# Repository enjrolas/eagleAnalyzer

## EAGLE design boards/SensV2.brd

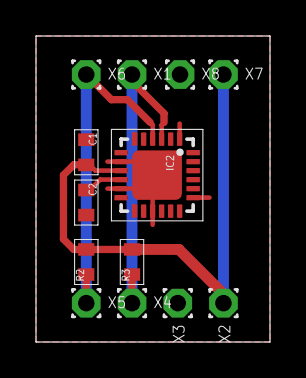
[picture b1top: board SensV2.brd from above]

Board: 2 copper layers, 13.0 x 17.0 mm, 13 parts (0 on the bottom side), 5 nets.

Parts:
C1: 100n; 0603
C2: 4u7; 0603
IC2: QFN24
R2, R3: 4k7; 0603
X1, X3, X4, X5, X6, X8: GND; T1.6/0.9
X2, X7: 3v3; T1.6/0.9

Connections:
+3V3: C1.2, IC2.9, R2.2, R3.2, X2.1, X7.1
GND: C1.1, C2.2, IC2.1, IC2.8, IC2.11, IC2.15, IC2.19, IC2.EXP, X3.1, X8.1
unnamed: C2.1, IC2.10
SCL: IC2.3, R3.1, X1.1, X4.1
SDA: IC2.4, R2.1, X5.1, X6.1

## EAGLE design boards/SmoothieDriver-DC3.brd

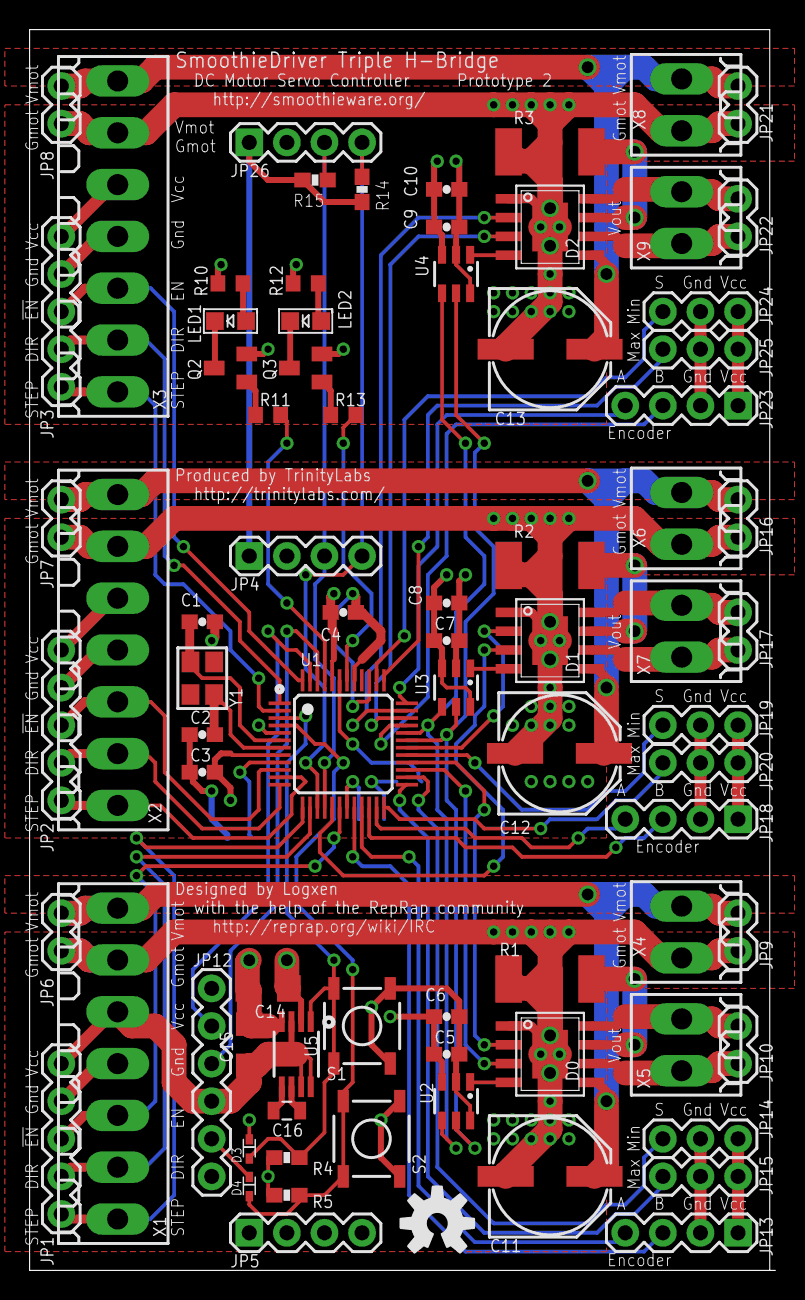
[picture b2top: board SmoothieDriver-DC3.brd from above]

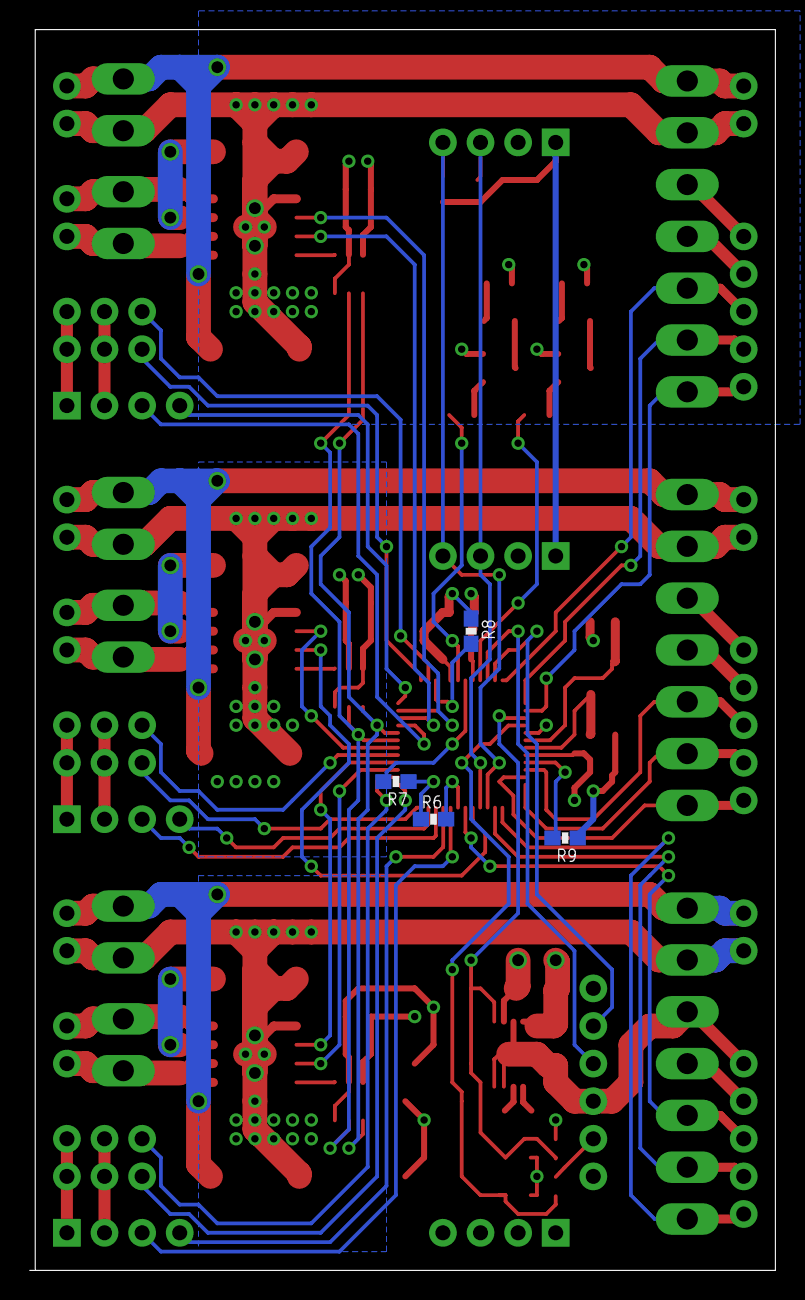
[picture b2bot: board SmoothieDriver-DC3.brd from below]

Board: 4 copper layers, 50.0 x 83.8 mm, 89 parts (5 on the bottom side), 75 nets.

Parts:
C1, C2: 18pF; 0603-CAP
C3, C4, C5, C7, C9: 0.1uF; 0603-CAP
C6, C8, C10: 10uF; 0603-CAP
C11, C12, C13: 100uF; PANASONIC_E
C14, C15: 10uF; 1206
C16: 1uF; 0805
D0, D1, D2: A4950; SOICN8-PAD
D0_GMOT: NET_LINK
D3, D4: 1N4148; SOD523
JP1: LOGIC_0; 1X05
JP2: LOGIC_1; 1X05
JP3: LOGIC_2; 1X05
JP4, JP5, JP26: I2C; 1X04
JP6, JP7, JP8: VMOT; 1X02
JP9: D0_PWR; 1X02
JP10: D0_OUT; 1X02
JP12: UART; 1X06
JP13: D0_ENC; 1X04
JP14: D0_MIN; 1X03
JP15: D0_MAX; 1X03
JP16: D1_PWR; 1X02
JP17: D1_OUT; 1X02
JP18: D1_ENC; 1X04
JP19: D1_MIN; 1X03
JP20: D1_MAX; 1X03
JP21: D2_PWR; 1X02
JP22: D2_OUT; 1X02
JP23: D2_ENC; 1X04
JP24: D2_MIN; 1X03
JP25: D2_MAX; 1X03
LED1, LED2: 20mA; CHIPLED_0805
Q2, Q3: 25mA; SOT23
R1, R2, R3: 0.1 Ohm; R2512
R4, R5: 10kOhm; 0603-RES
R6: ADD0; 0603-RES
R7: ADD1; 0603-RES
R8: ADD2; 0603-RES
R9: ADD3; 0603-RES
R10, R12: 75 Ohm; R0603
R11, R13: 1200 Ohm; R0603
R14, R15: NP; 0603-RES
S1: RESET; TACTILE_SWITCH_SMD
S2: ISP; TACTILE_SWITCH_SMD
U1: LPC1114FBD48; LQFP48
U2, U3: MCP4725A0; SOT23-6
U4: MCP4725A1; SOT23-6
U5: MCP1252-33X40I/MS; MSOP8_0.65MM
U$15: OSHW-LOGOM; OSHW-LOGO-M
U$22, U$23, U$24, U$25, U$26: NET_LINK
X1: DRIVER_0; 180-7
X2: DRIVER_1; 180-7
X3: DRIVER_2; 180-7
X4: D0_PWR; 180-2
X5: D0_OUT; 180-2
X6: D1_PWR; 180-2
X7: D1_OUT; 180-2
X8: D2_PWR; 180-2
X9: D2_OUT; 180-2
Y1: 12MHz; CRYSTAL_3.2X2.5

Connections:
ACC_SCL: U1.31, U2.5, U3.5, U4.5
ACC_SDA: U1.32, U2.4, U3.4, U4.4
ADD0: R6.2, U1.19
ADD1: R7.2, U1.43
ADD2: R8.2, U1.39
ADD3: R9.2, U1.9
D0_DIR: JP1.4, U1.14, X1.6
D0_EN: JP1.3, U1.18, X1.5
D0_ENC1: JP13.3, U1.20
D0_ENC2: JP13.4, U1.21
D0_GMOT: C11.-, D0.1, D0_GMOT.P$1, JP6.2, JP9.2, X1.2, X4.1
D0_IN1: D0.3, U1.27
D0_IN2: D0.2, U1.28
D0_LSS: D0.7, R1.2
D0_MAX: JP15.3, U1.25
D0_MIN: JP14.3, U1.26
D0_OUT1: D0.6, JP10.1, X5.1
D0_OUT2: D0.8, JP10.2, X5.2
D0_STEP: JP1.5, U1.13, X1.7
D0_VMOT: C11.+, D0.5, JP6.1, JP9.1, X1.1, X4.2
D0_VREF: D0.4, U2.1
D1_DIR: JP2.4, U1.12, X2.6
D1_EN: JP2.3, U1.10, X2.5
D1_ENC1: JP18.3, U1.22
D1_ENC2: JP18.4, U1.23
D1_GMOT: C12.-, D1.1, JP7.2, JP16.2, U$23.P$1, X2.2, X6.1
D1_IN1: D1.3, U1.17
D1_IN2: D1.2, U1.30
D1_LSS: D1.7, R2.2
D1_LSS1: D2.7, R3.2
D1_MAX: JP20.3, U1.24
D1_MIN: JP19.3, U1.29
D1_OUT1: D1.6, JP17.1, X7.1
D1_OUT2: D1.8, JP17.2, X7.2
D1_STEP: JP2.5, U1.11, X2.7
D1_VMOT: C12.+, D1.5, JP7.1, JP16.1, X2.1, X6.2
D1_VREF: D1.4, U3.1
D2_DIR: JP3.4, U1.1, X3.6
D2_EN: JP3.3, U1.48, X3.5
D2_ENC1: JP23.3, U1.33
D2_ENC2: JP23.4, U1.36
D2_GMOT: C13.-, D2.1, JP8.2, JP21.2, U$26.P$1, X3.2, X8.1
D2_IN1: D2.3, U1.34
D2_IN2: D2.2, U1.35
D2_MAX: JP25.3, U1.37
D2_MIN: JP24.3, U1.38
D2_OUT1: D2.6, JP22.1, X9.1
D2_OUT2: D2.8, JP22.2, X9.2
D2_STEP: JP3.5, U1.2, X3.7
D2_VMOT: C13.+, D2.5, JP8.1, JP21.1, X3.1, X8.2
D2_VREF: D2.4, U4.1
DTR: D3.C, JP12.6
GND: C1.1, C2.1, C3.1, C4.1, C5.2, C6.2, C7.2, C8.2, C9.2, C10.2, C14.2, C15.2, D0.PAD, D0_GMOT.P$2, D1.PAD, D2.PAD, JP1.2, JP2.2, JP3.2, JP4.2, JP5.2, JP12.1, JP13.2, JP14.2, JP15.2, JP18.2, JP19.2, JP20.2, JP23.2, JP24.2, JP25.2, JP26.2, Q2.2, Q3.2, R1.1, R2.1, R3.1, R6.1, R7.1, R8.1, R9.1, S1.1, S1.2, S2.1, S2.2, U1.5, U1.41, U2.2, U2.6, U3.2, U4.2, U4.6, U5.4, U$22.P$1, U$22.P$2, U$23.P$2, U$24.P$1, U$24.P$2, U$25.P$1, U$25.P$2, U$26.P$2, X1.4, X2.4, X3.4
ISP: D4.A, R5.1, S2.3, S2.4, U1.4
LED0: R11.2, U1.45
LED1: R13.2, U1.42
unnamed: LED1.A, R10.2
unnamed: LED1.C, Q2.3
unnamed: Q2.1, R11.1
unnamed: Q3.1, R13.1
unnamed: LED2.A, R12.2
unnamed: LED2.C, Q3.3
PWRREG_C+: C16.1, U5.6
PWRREG_C-: C16.2, U5.5
RESET: D3.A, R4.1, S1.3, S1.4, U1.3, U5.1
RTS: D4.C, JP12.2
RXD: JP12.4, U1.46
SCL: JP4.4, JP5.4, JP26.4, R14.1, U1.15
SDA: JP4.3, JP5.3, JP26.3, R15.1, U1.16
TXD: JP12.5, U1.47
VCC: C3.2, C4.2, C5.1, C6.1, C7.1, C8.1, C9.1, C10.1, C14.1, JP13.1, JP14.1, JP15.1, JP18.1, JP19.1, JP20.1, JP23.1, JP24.1, JP25.1, R4.2, R5.2, R10.1, R12.1, U1.8, U1.44, U2.3, U3.3, U3.6, U4.3, U5.2
VDD: JP4.1, JP5.1, JP26.1, R14.2, R15.2
VIN: C15.1, JP1.1, JP2.1, JP3.1, JP12.3, U5.3, U5.7, U5.8, X1.3, X2.3, X3.3
XTALIN: C1.2, U1.6, Y1.2
XTALOUT: C2.2, U1.7, Y1.1

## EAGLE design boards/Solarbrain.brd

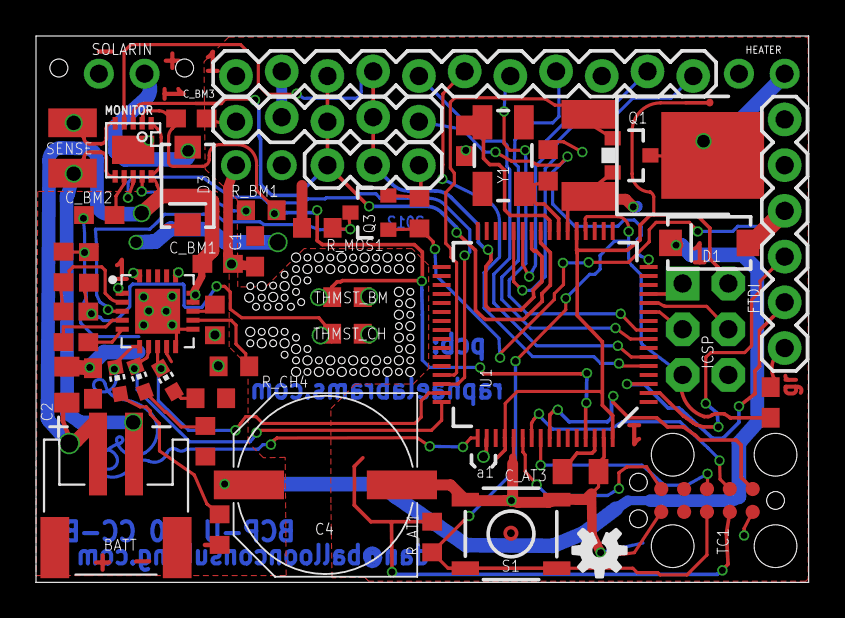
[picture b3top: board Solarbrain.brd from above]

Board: 2 copper layers, 42.9 x 30.4 mm, 51 parts (0 on the bottom side), 48 nets.

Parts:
AUTORESET: .1uf; C0603
BATT: JST-PH-2-SMT-RA
C1: 10uF; C0603
C2: 10uF; C0805K
C3: 10uF/10V; C0603
C4: 4700uF/10V; PANASONIC_G
CHRG/LBO: ORANGE; CHIP-LED0603
C_AT1: 22pf; C0603K
C_AT2: 22pf; C0603
C_AT3: 10uF; C0805K
C_BM1, C_BM2: .1uF/10V; C0603
C_BM3: 10uF/10V; C0603
D1: 1amp; SMA-DIODE
D3: 3amp; SMA-DIODE
DONE: GREEN; CHIP-LED0603
FTDI: FTDI_BASICPTH; FTDI_BASIC
HEATER: 1X02_ROUND
IC1: MCP73871; QFN20_4MM
ICSP: AVR_SPI_PRG_6NS; 2X3-NS
JP1: 1X03
JP3: M11LOCK; 1X11_LOCK
JP8: 1X05_LOCK
LOAD: 1X02_ROUND
MONITOR: MAX17047_17050_BATTERY_GAS_GAUGE; TDFN_10_3X3MM
PWR: RED; CHIP-LED0603
Q1, Q3: MOSFET-NCHANNELSMD; SOT23-3
Q2: MOSFET-NCHANNELFDD8580; DPAK
R_AT1: 1K; R0603
R_BM1: 1K; R0603
R_CH1: 270K; R0603
R_CH2, R_CH4: 100K; R0603
R_CH3: 1k; R0603
R_CH5: 1K; R0603
R_CH6: 150K; R0603
R_LED1, R_LED2, R_LED3: 1K; R0603
R_MOS1, R_MOS2: 1K; R0603
S1: TACTILE_SWITCH_SMD
SENSE: R3225
SOLARIN: DCIN; 1X02_ROUND
TC1: TC2050-IDC
THMST_BM: R0603
THMST_CH: R0603
U1: ATMEGA128_SMD; TQFP64
U$1: OSHW-LOGO-S
Y1: CRYSTAL-SMD-5X3

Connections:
3.3V: C1.1, HEATER.2, IC1.P$1, IC1.P$20, ICSP.2, JP3.10, JP8.4, LOAD.1, R_AT1.2, R_MOS1.2, TC1.4, U1.21, U1.52, U1.64
#PG: IC1.P$6, PWR.C, U1.49
BATT: BATT.1, C2.1, C_BM1.1, IC1.P$14, IC1.P$15, IC1.P$16, MONITOR.P$1, MONITOR.P$10
CSP: BATT.2, MONITOR.P$6, SENSE.2
DTR: AUTORESET.2, FTDI.DTR
GND: C1.2, C2.2, C3.2, C4.-, C_AT1.2, C_AT2.2, C_AT3.2, C_BM1.2, C_BM2.2, C_BM3.2, FTDI.GND, IC1.P$10, IC1.P$11, IC1.P$21, ICSP.6, JP1.1, JP3.11, JP8.5, LOAD.2, MONITOR.P$5, MONITOR.P$11, Q1.2, Q2.3, Q3.2, R_CH2.2, R_CH3.1, R_CH4.1, R_CH6.1, R_MOS2.1, S1.3, S1.4, SENSE.1, SOLARIN.1, TC1.2, TC1.10, THMST_BM.2, THMST_CH.1, U1.22, U1.53, U1.63
MISO: ICSP.1, U1.13
MOSI: ICSP.4, U1.12
unnamed: D1.A, FTDI.VCC, Q3.1, R_MOS2.2
unnamed: C_AT1.1, U1.23, Y1.3
unnamed: IC1.P$5, R_CH5.1
unnamed: R_CH5.2, R_CH6.2, THMST_CH.2
unnamed: C_AT2.1, U1.24, Y1.1
unnamed: CHRG/LBO.A, R_LED1.1
unnamed: DONE.A, R_LED2.1
unnamed: PWR.A, R_LED3.1
unnamed: MONITOR.P$8, U1.46
unnamed: C_AT3.1, U1.62
unnamed: HEATER.1, Q1.3, Q2.4
unnamed: MONITOR.P$9, R_BM1.2
unnamed: D3.A, SOLARIN.2
unnamed: C_BM2.1, MONITOR.P$7
PROG1: IC1.P$13, R_CH3.2
PROG3: IC1.P$12, R_CH4.2
RESET: AUTORESET.1, ICSP.5, R_AT1.1, S1.1, S1.2, TC1.6, U1.20
RX: FTDI.RXI, U1.3
SAT_CTS: JP3.7, U1.6
SAT_NA: JP3.5, U1.9
SAT_RI: JP3.4, U1.8
SAT_RTS: JP3.6, U1.5
SCK: ICSP.3, U1.11
SCL: JP1.3, JP3.9, JP8.3, MONITOR.P$3, U1.25
SDA: JP1.2, JP3.8, JP8.2, MONITOR.P$4, U1.26
SEL: IC1.P$3, Q3.3, R_MOS1.1
SER_FROM_SAT: JP3.2, U1.27
SER_TO_SAT: JP3.1, U1.28
SLEEP: JP8.1, U1.16
STAT1: CHRG/LBO.C, IC1.P$8, U1.47
STAT2: DONE.C, IC1.P$7, U1.48
TCK: TC1.1, U1.57
TDI: TC1.9, U1.54
TDO: TC1.3, U1.55
THERM_ANALOG: C_BM3.1, MONITOR.P$2, R_BM1.1, THMST_BM.1, U1.61
THE_HEAT_ON: Q1.1, Q2.1, U1.45
TMS: TC1.5, U1.56
TX: FTDI.TXO, U1.2
VCC: C3.1, C4.+, D1.C, D3.C, IC1.P$4, IC1.P$9, IC1.P$17, IC1.P$18, IC1.P$19, R_CH1.2, R_LED1.2, R_LED2.2, R_LED3.2
VPCC: IC1.P$2, R_CH1.1, R_CH2.1

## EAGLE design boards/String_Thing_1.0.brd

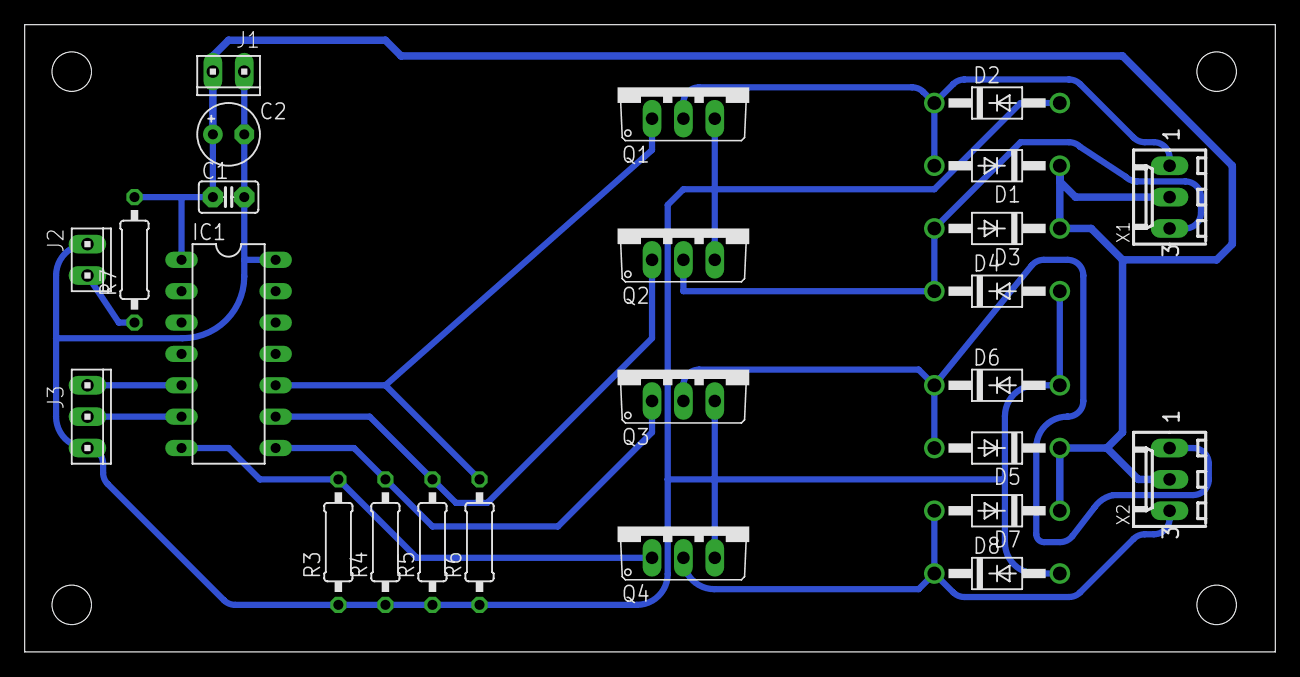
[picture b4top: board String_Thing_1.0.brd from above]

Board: 2 copper layers, 101.3 x 50.8 mm, 25 parts (0 on the bottom side), 13 nets.

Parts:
C1: C025-025X050
C2: E2,5-5
D1, D2, D3, D4, D5, D6, D7, D8: 1N4004; DO41-10
IC1: PIC16F676P; DIL14
J1, J2: 10X02MTA
J3: 10X03MTA
Q1, Q2, Q3, Q4: TO220V
R3, R4, R5, R6, R7: 0207/10
X1, X2: 22-27-2031-03; 6410-03

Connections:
GND: C1.2, C2.-, D2.A, D4.A, D6.A, D8.A, IC1.14, J1.2, J2.2, J3.1, Q1.3, Q2.3, Q3.3, Q4.3, R3.1, R4.1, R5.1, R6.1
unnamed: IC1.7, Q4.1, R3.2
unnamed: IC1.8, Q3.1, R4.2
unnamed: IC1.9, Q2.1, R5.2
unnamed: IC1.10, Q1.1, R6.2
unnamed: D1.A, D2.C, Q1.2, X1.1
unnamed: D3.A, D4.C, Q2.2, X1.3
unnamed: D5.A, D6.C, Q3.2, X2.1
unnamed: D7.A, D8.C, Q4.2, X2.3
unnamed: J2.1, R7.1
unnamed: IC1.5, J3.3
unnamed: IC1.6, J3.2
VCC: C1.1, C2.+, D1.C, D3.C, D5.C, D7.C, IC1.1, J1.1, R7.2, X1.2, X2.2

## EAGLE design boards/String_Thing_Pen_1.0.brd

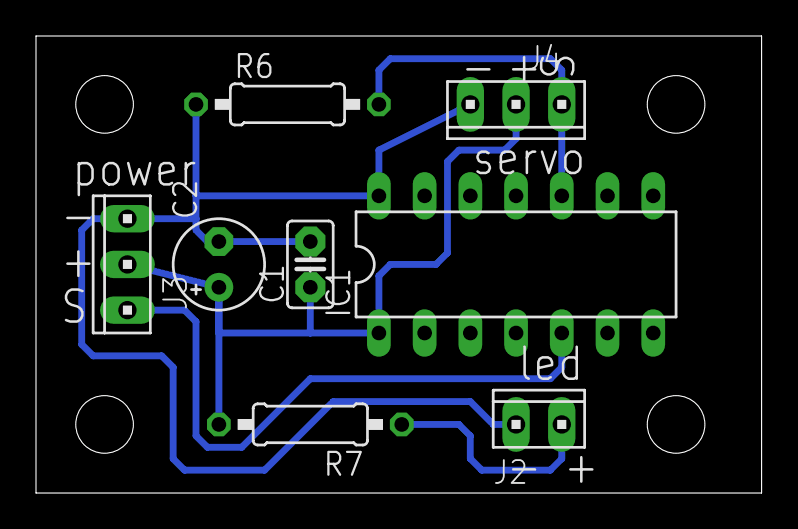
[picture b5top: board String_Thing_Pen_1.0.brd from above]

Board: 2 copper layers, 40.3 x 25.4 mm, 8 parts (0 on the bottom side), 5 nets.

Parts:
C1: C025-025X050
C2: E2,5-5
IC1: PIC16F676P; DIL14
J2: 10X02MTA
J3, J4: 10X03MTA
R6, R7: 0207/10

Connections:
GND: C1.2, C2.-, IC1.14, J2.2, J3.1, J4.1, R6.1
unnamed: IC1.10, J4.3, R6.2
unnamed: J2.1, R7.1
unnamed: IC1.5, J3.3
VCC: C1.1, C2.+, IC1.1, J3.2, J4.2, R7.2

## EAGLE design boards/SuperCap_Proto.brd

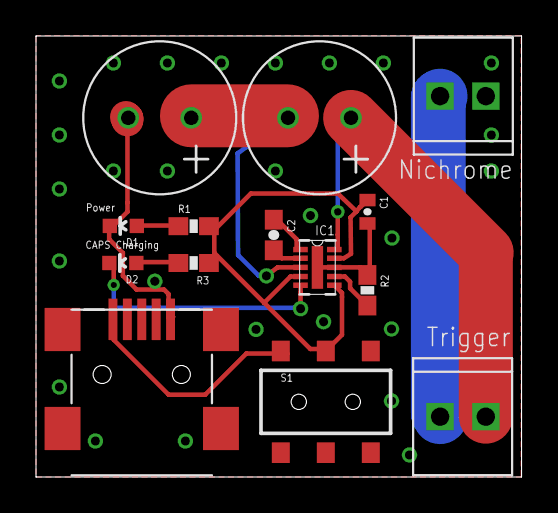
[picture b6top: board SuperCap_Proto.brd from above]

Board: 2 copper layers, 27.0 x 24.5 mm, 14 parts (0 on the bottom side), 12 nets.

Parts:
C1: C1005X5R0J225K050BC; 0402-CAP
C2: 0603ZD105KAT2A; 0603-CAP
C3, C4: HV0830-2R7605-R; CAP_POL_RADIAL_6F_2.7V
CN1: USB-MINIB
CUTDOWN: M022.54MM_SCREWTERM; 1X02_2.54_SCREWTERM
CUT_SW: M022.54MM_SCREWTERM; 1X02_2.54_SCREWTERM
D1: LTW-C193TS5; LED-0603
D2: APT1608SRCPRV; LED-0603
IC1: LTC3225EDDB-1TRPBF; DFN300X200X80
R1: 390; 0603-RES
R2: 12k; 0603-RES
R3: 180; 0603-RES
S1: AYZ0202AGRL; AYZ0202

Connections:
5V: C1.1, IC1.4, IC1.6, IC1.9, R1.2, R3.1, S1.2
GND: C1.2, C4.P$2, CN1.GND, CUTDOWN.P2, D1.C, IC1.8, IC1.11, R2.1
unnamed: CUTDOWN.P1, CUT_SW.P2
unnamed: C3.P$1, CUT_SW.P1, IC1.10
unnamed: CN1.VBUS, S1.1
unnamed: D2.C, IC1.5
unnamed: IC1.7, R2.2
unnamed: D2.A, R3.2
unnamed: D1.A, R1.1
unnamed: C3.P$2, C4.P$1, IC1.3
unnamed: C2.1, IC1.1
unnamed: C2.2, IC1.2

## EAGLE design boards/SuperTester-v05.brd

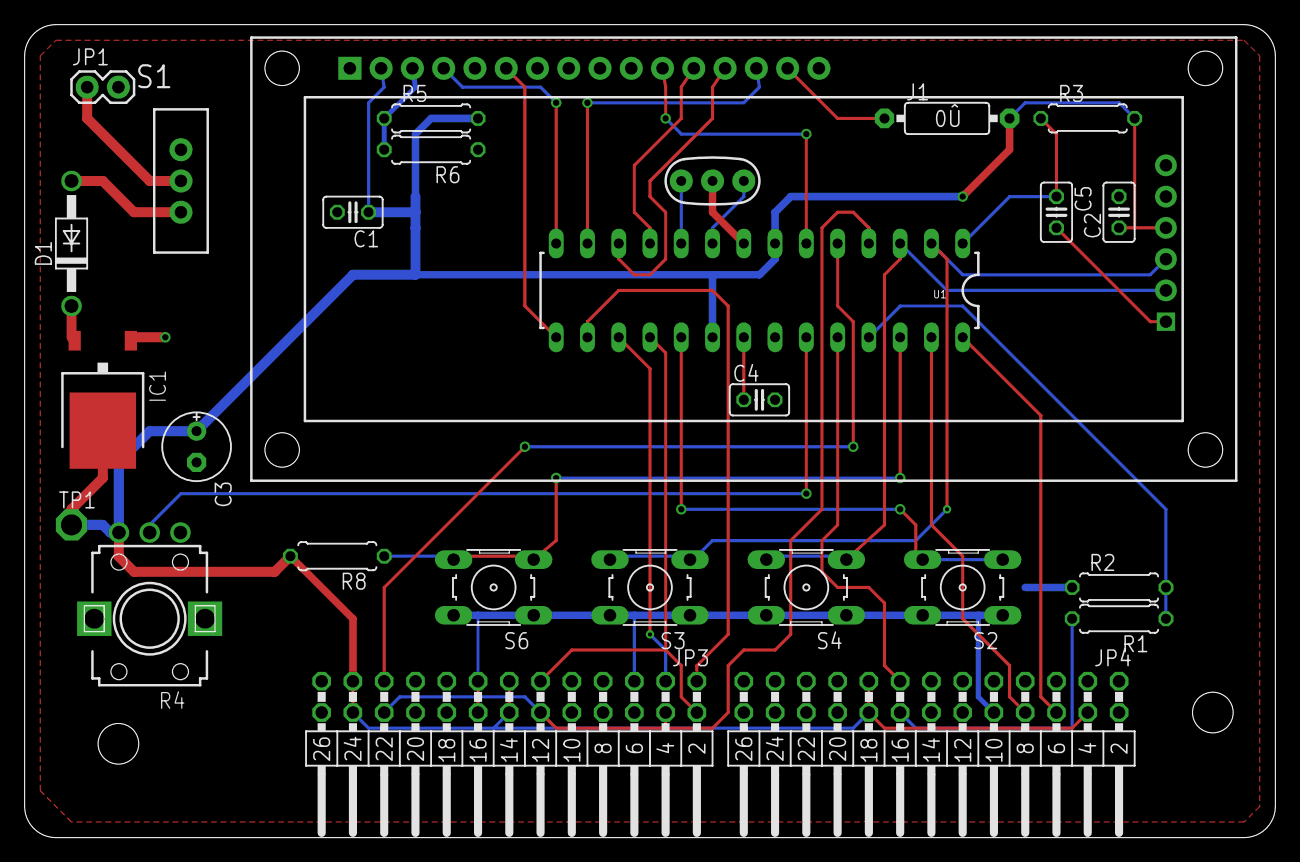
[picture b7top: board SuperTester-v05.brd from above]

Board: 2 copper layers, 101.6 x 66.0 mm, 31 parts (1 on the bottom side), 33 nets.

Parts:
C1, C2, C4, C5: 100nF; C025-025X050
C3: 10uF; E2,5-6E
D1: 1N4004; DO41-10
FRAME1: FRAME-LETTER; CREATIVE_COMMONS
IC1: MC33269D-5.0; DPACK
J1: 0; 0R/10
JP1: 1X2 Header; 1X02
JP2: FTDI_DEVICE; FTDI_DEVICE_SIDE
JP3, JP4: 2X13 Rght Angle Hdr; MA13-2W
R1: 24K; 0207/7
R2: 1K; 0207/7
R3, R8: 10K; 0207/7
R4: 10K; EVUF
R5: 2.4K; 0207/7
R6: 510; 0207/7
S1: POWER; SWITCH-SPDT
S2, S3, S4, S6: B3F-1070; B3F-10XX
STANDOFF1, STANDOFF2: STAND-OFF
TP1: TPPAD1-17; P1-17
U1: ATMEGA328P_PDIP; DIL28-3
U2: LCD-16X2SILK; LCD-16X2
Y1: 16MHz; RESONATOR-PTH

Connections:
ACT1: JP2.P$3, S3.3, S3.4, U1.2
ACT2: JP2.P$2, S4.3, S4.4, U1.3
AIN0: R4.2, U1.23
AIN1: JP4.15, U1.24
AIN2: R1.1, R2.2, U1.25
AREF: C4.1, U1.21
BRIGHT: J1.1, U2.15
CON: R5.1, R6.2, U2.3
D4: U1.6, U2.11
D5: U1.11, U2.12
D6: U1.12, U2.13
D7: U1.13, U2.14
DIN1: JP3.4, JP3.12, JP3.22, U1.4
DIN2: JP3.2, JP3.11, U1.18
EN: U1.15, U2.6
GND: C1.2, C2.2, C3.-, C4.2, IC1.1, JP1.2, JP2.P$5, JP2.P$6, JP3.5, JP3.6, JP3.15, JP3.16, JP3.25, JP3.26, JP4.10, JP4.19, JP4.20, R2.1, R4.1, R6.1, S2.1, S2.2, S3.1, S3.2, S4.1, S4.2, S6.1, S6.2, U1.8, U1.22, U2.1, U2.5, U2.16, Y1.2
NEXT: S2.3, S2.4, U1.19
PREV: R8.1, S6.3, S6.4, U1.26
PWMOUT: JP3.21, U1.5
RESET: C5.1, R3.1, U1.1
RS: U1.14, U2.4
RST#: C5.2, JP2.P$1
SCALED_AIN: JP4.16, R1.2
SCL: JP4.6, U1.28
SDA: JP4.8, U1.27
SPIKE_FWD: JP3.1, U1.16
SPIKE_REV: JP3.3, U1.17
VB: D1.A, S1.3
VCC: C1.1, C2.1, C3.+, IC1.2, J1.2, JP2.P$4, JP3.13, JP3.14, JP3.23, JP3.24, JP4.4, JP4.17, JP4.18, R3.2, R4.3, R5.2, R8.2, TP1.TP, U1.7, U1.20, U2.2
VIN: D1.C, IC1.3
V_BATT: JP1.1, S1.2
XTAL1: U1.9, Y1.1
XTAL2: U1.10, Y1.3

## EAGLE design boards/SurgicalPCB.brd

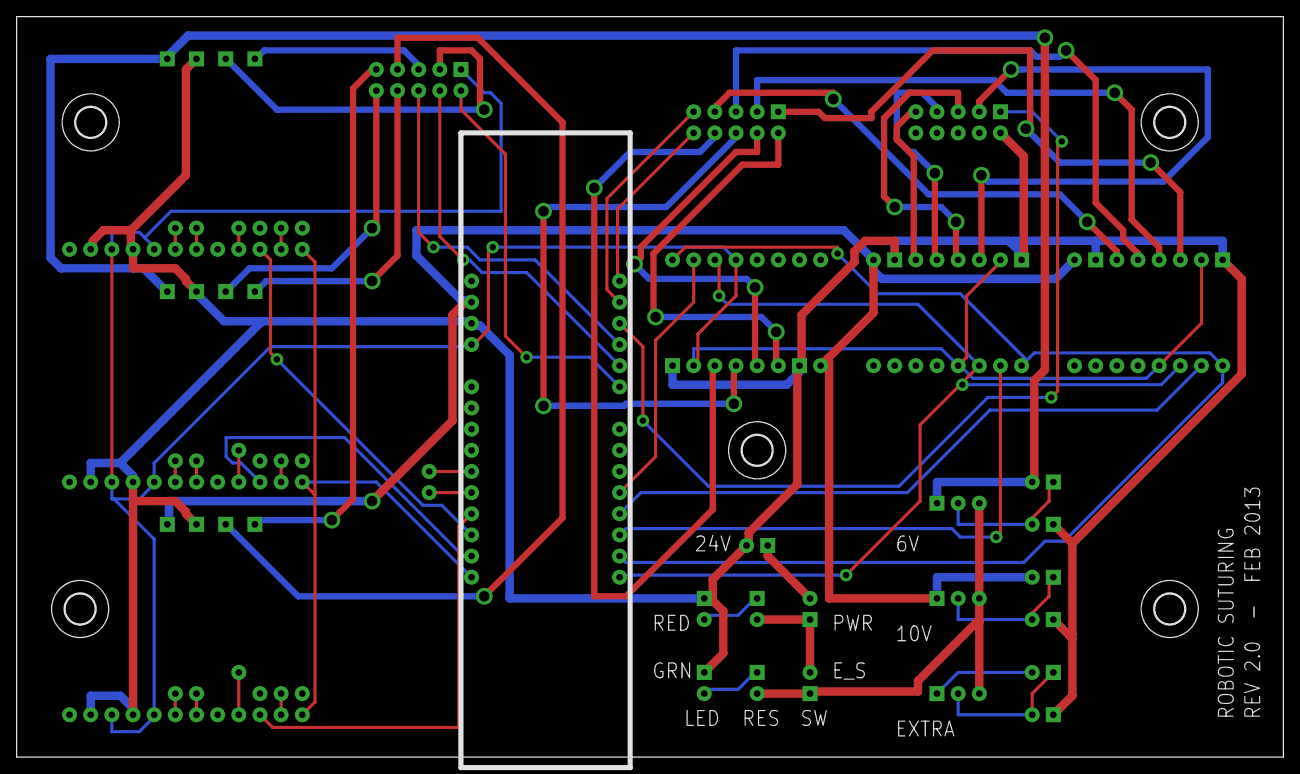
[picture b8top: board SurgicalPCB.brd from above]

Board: 2 copper layers, 152.1 x 88.9 mm, 36 parts (0 on the bottom side), 60 nets.

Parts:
6V, 10V: V_REG
EV: V_REG
E_STOP: RESISTOR
LED_GREEN: RESISTOR
LED_R: RESISTOR
LED_RES: RESISTOR
LED_RES_G: RESISTOR
POWERPLUG: RESISTOR
POWER_SWITCH: RESISTOR
RES6-1: RESISTOR
RES_6-2, RES_10-1, RES_10-2: RESISTOR
RES_EV-1, RES_EV-2: RESISTOR
U$1, U$2, U$3: A4955
U$4: BOARDUINOSTD; BOARDUINO
U$5, U$6, U$7: MC33926
U$8, U$9, U$10: 2_5_RIBBON
U$11, U$13, U$15, U$16, U$17: 3,6
U$14, U$23, U$24, U$25, U$26: PROPE_HOLE

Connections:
6V_RAIL: 6V.VOUT, RES6-1.VIN, U$5.M_VIN, U$6.M_VIN
10V_RAIL: 10V.VOUT, RES_10-1.VIN, U$1.VMOT, U$2.VMOT, U$3.VMOT, U$4.VIN, U$7.M_VIN
24V_1: POWERPLUG.VOUT, POWER_SWITCH.VIN
24V_2: E_STOP.VIN, LED_RES.VIN, POWER_SWITCH.VOUT
24V_3: LED_R.VIN, LED_RES.VOUT
24V_4: 6V.VIN, 10V.VIN, EV.VIN, E_STOP.VOUT, LED_RES_G.VIN
24V_5: LED_GREEN.VIN, LED_RES_G.VOUT
GND: LED_GREEN.VOUT, LED_R.VOUT, POWERPLUG.VIN, RES_6-2.VOUT, RES_10-2.VOUT, RES_EV-2.VOUT, U$1.GND, U$1.GND_2, U$2.GND, U$2.GND_2, U$3.GND, U$3.GND_2, U$4.GND_3, U$5.GND, U$5.IN2, U$5.M_GND, U$6.GND, U$6.IN2, U$6.M_GND, U$7.GND, U$7.IN2, U$7.M_GND, U$9.2
LOGIC_HIGH_RAIL: U$1.!RST, U$1.VDD, U$2.!RST, U$2.VDD, U$3.!RST, U$3.VDD, U$4.5V_2, U$5.IN1, U$5.VDD, U$6.IN1, U$6.VDD, U$7.IN1, U$7.VDD, U$8.1
unnamed: U$3.STEP, U$4.12
unnamed: U$1.!SLP, U$2.!SLP, U$3.!SLP, U$4.D8
unnamed: U$1.DIT, U$2.DIT, U$3.DIT, U$4.D9
unnamed: U$1.STEP, U$4.10
unnamed: U$2.STEP, U$4.11
unnamed: U$7.FB, U$14.P$1
unnamed: U$6.FB, U$23.P$1
unnamed: U$5.JP_PWM/D2, U$5.PWN/D2
unnamed: U$5.JP_PWM/D1, U$5.PWM/D1
unnamed: U$5.JP_SLEW, U$5.SLEW
unnamed: U$5.FB, U$24.P$1
unnamed: U$4.D3, U$25.P$1
unnamed: U$6.JP_PWM/D2, U$6.PWN/D2
unnamed: U$6.JP_PWM/D1, U$6.PWM/D1
unnamed: U$6.JP_SLEW, U$6.SLEW
unnamed: U$4.D2, U$26.P$1
unnamed: U$7.JP_PWM/D2, U$7.PWN/D2
unnamed: U$7.JP_PWM/D1, U$7.PWM/D1
unnamed: U$7.JP_SLEW, U$7.SLEW
unnamed: U$4.D7, U$5.INV, U$6.INV, U$7.INV
unnamed: U$5.M_OUT2, U$8.10
unnamed: U$4.D6, U$5.EN
unnamed: U$4.D5, U$6.EN
unnamed: U$4.D4, U$7.EN
unnamed: U$5.M_OUT1, U$8.8
unnamed: U$6.M_OUT2, U$8.3
unnamed: U$6.M_OUT1, U$8.5
unnamed: U$7.M_OUT2, U$8.7
unnamed: U$7.M_OUT1, U$8.9
unnamed: U$4.A2, U$8.6
unnamed: U$4.A1, U$8.4
unnamed: U$4.A0, U$8.2
unnamed: U$3.2B, U$10.2
unnamed: U$3.2A, U$10.4
unnamed: U$3.1A, U$10.6
unnamed: U$3.1B, U$10.8
unnamed: U$4.A5, U$10.10
unnamed: U$2.1B, U$10.1
unnamed: U$2.1A, U$10.3
unnamed: U$2.2A, U$10.5
unnamed: U$2.2B, U$10.7
unnamed: U$4.A4, U$10.9
unnamed: U$1.2B, U$9.9
unnamed: U$1.2A, U$9.7
unnamed: U$1.1A, U$9.5
unnamed: U$1.1B, U$9.3
unnamed: U$4.A3, U$9.1
unnamed: 10V.ADJ, RES_10-1.VOUT, RES_10-2.VIN
unnamed: 6V.ADJ, RES6-1.VOUT, RES_6-2.VIN
unnamed: EV.VOUT, RES_EV-1.VIN
unnamed: EV.ADJ, RES_EV-1.VOUT, RES_EV-2.VIN

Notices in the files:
boards/Solarbrain.brd:
BCP-U 1.0 CC-BY
parts and their libraries:
microbuilder: This work is placed in the public domain, and may be freely used for commercial and non-commercial work with the following conditions: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
SparkFun-Capacitors: Licensing: CC v3.0 Share-Alike You are welcome to use this library for commercial purposes.
